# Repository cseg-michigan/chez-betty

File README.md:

Chez Betty
==========

Chez Betty is a mini, cooperative food store where users can deposit money to their account
and use it to purchase food and other items. The system is linked
to the UMich ldap server so users can swipe their M-Card to login.

UMich version is an homage to UCSD's [Chez Bob](http://chezbob.ucsd.edu/).
Chez Betty runs [here](http://chezbetty.store).

Chez Betty is written as a Python web app designed to run on a server with
a browser based user interface. It supports cash and credit card deposits. The
user interface expects a card swiper and barcode scanner to be attached to
the machine. See the list at the end of this README for products we use.
To test / demo the system without hardware, turn on "Demo mode" in the admin
interface.

Installation
------------

The Chez Betty application is developed using Python Pyramid. To get a
development environment set up, do the following:

1. Clone this repository

        git clone https://github.com/um-cseg/chez-betty.git

2. Install system dependencies:

        # Ubuntu 15.10
        sudo apt-get install postgresql postgresql-server-dev-9.4 libjpeg-dev
        # Ubuntu 16.10
        sudo apt-get install postgresql postgresql-server-dev-9.5 libjpeg-dev

1. Setup virtualenv with Python3:

        cd chez-betty

        # Python cannot decide on how it wants to do this. So
        # we have multiple iterations that we have tried.
        ## Way back:
        # virtualenv .
        ## Python3.3:
        # python3 -m venv .
        # ^ *not* pyvenv ., that installed python2 in my venv for w/e reason
        ## Newest (only do this with Python 3.4+):
        # pyvenv-3.5 venv
        ## Python 3.6 changes it again!
        #python3.6 -m venv
        ## And for 3.7
        python3.7 -m venv venv

        source venv/bin/activate

2. Install the dependencies:

        # Note, this step *must* be run before setup.py. The latter will use
        # easy_install to install requirements instead of pip, which will
        # break some packages (e.g. stripe). The argument should be the root
        # directory of the project.
        pip install -e .

2. Setup the development environment

        python setup.py develop

3. Update `development.ini` to set config information and passwords.

        cp development.ini.example development.ini
        [edit development.ini]

    You will want to use a postgres database. Likely, your development.ini file
    will need to be updated to have this for the database:

        sqlalchemy.url = postgresql://bradjc@localhost:5432/chezbetty

    To create that database, do something like:

        psql
        > create database chezbetty;

3. Setup the database:

        python chezbetty/initializedb.py development.ini

4. Install bower and bower-install

        # Note: Distro copies of node tend to fall behind really quickly.
        # You are better off using a copy of node/npm installed directly:
        # http://nodejs.org/
        # https://github.com/npm/npm
        sudo npm install bower bower-installer -g

5. Get all css/js dependencies

        bower-installer

4. Run the webserver:

        pserve development.ini
        # n.b. pserve will be in your path if your virtualenv is active

### LDAP

TODO: add information about how to setup LDAP connection.

### Bitcoin

TODO: add info about how to setup bitcoin/coinbase.

Usage
-----

View the client interface using

    http://127.0.0.1:6543

View the admin interface using

    http://127.0.0.1:6543/admin
    username: admin
    password: chezbettyadmin

Tools
-----

Chez Betty currently runs using:

- Intel Nuc with case - Running Ubuntu.
- [Magnetic Strip Reader](https://www.cdw.com/shop/products/MagTek-SureSwipe-Reader-USB-HID-Keyboard-Interface-magnetic-card-reader/1140626.aspx) - Acts as a keyboard input.
- [Barcode Scanner](https://www.cdw.com/shop/products/Motorola-LS2208-barcode-scanner-scanner-and-USB-cable-included/3021140.aspx) - Also keyboard input.
- [Touchscreen Monitor](http://www.amazon.com/ViewSonic-TD2220-22-Inch-LED-Lit-Display/dp/B009F1IKFC) - Acts as a mouse.

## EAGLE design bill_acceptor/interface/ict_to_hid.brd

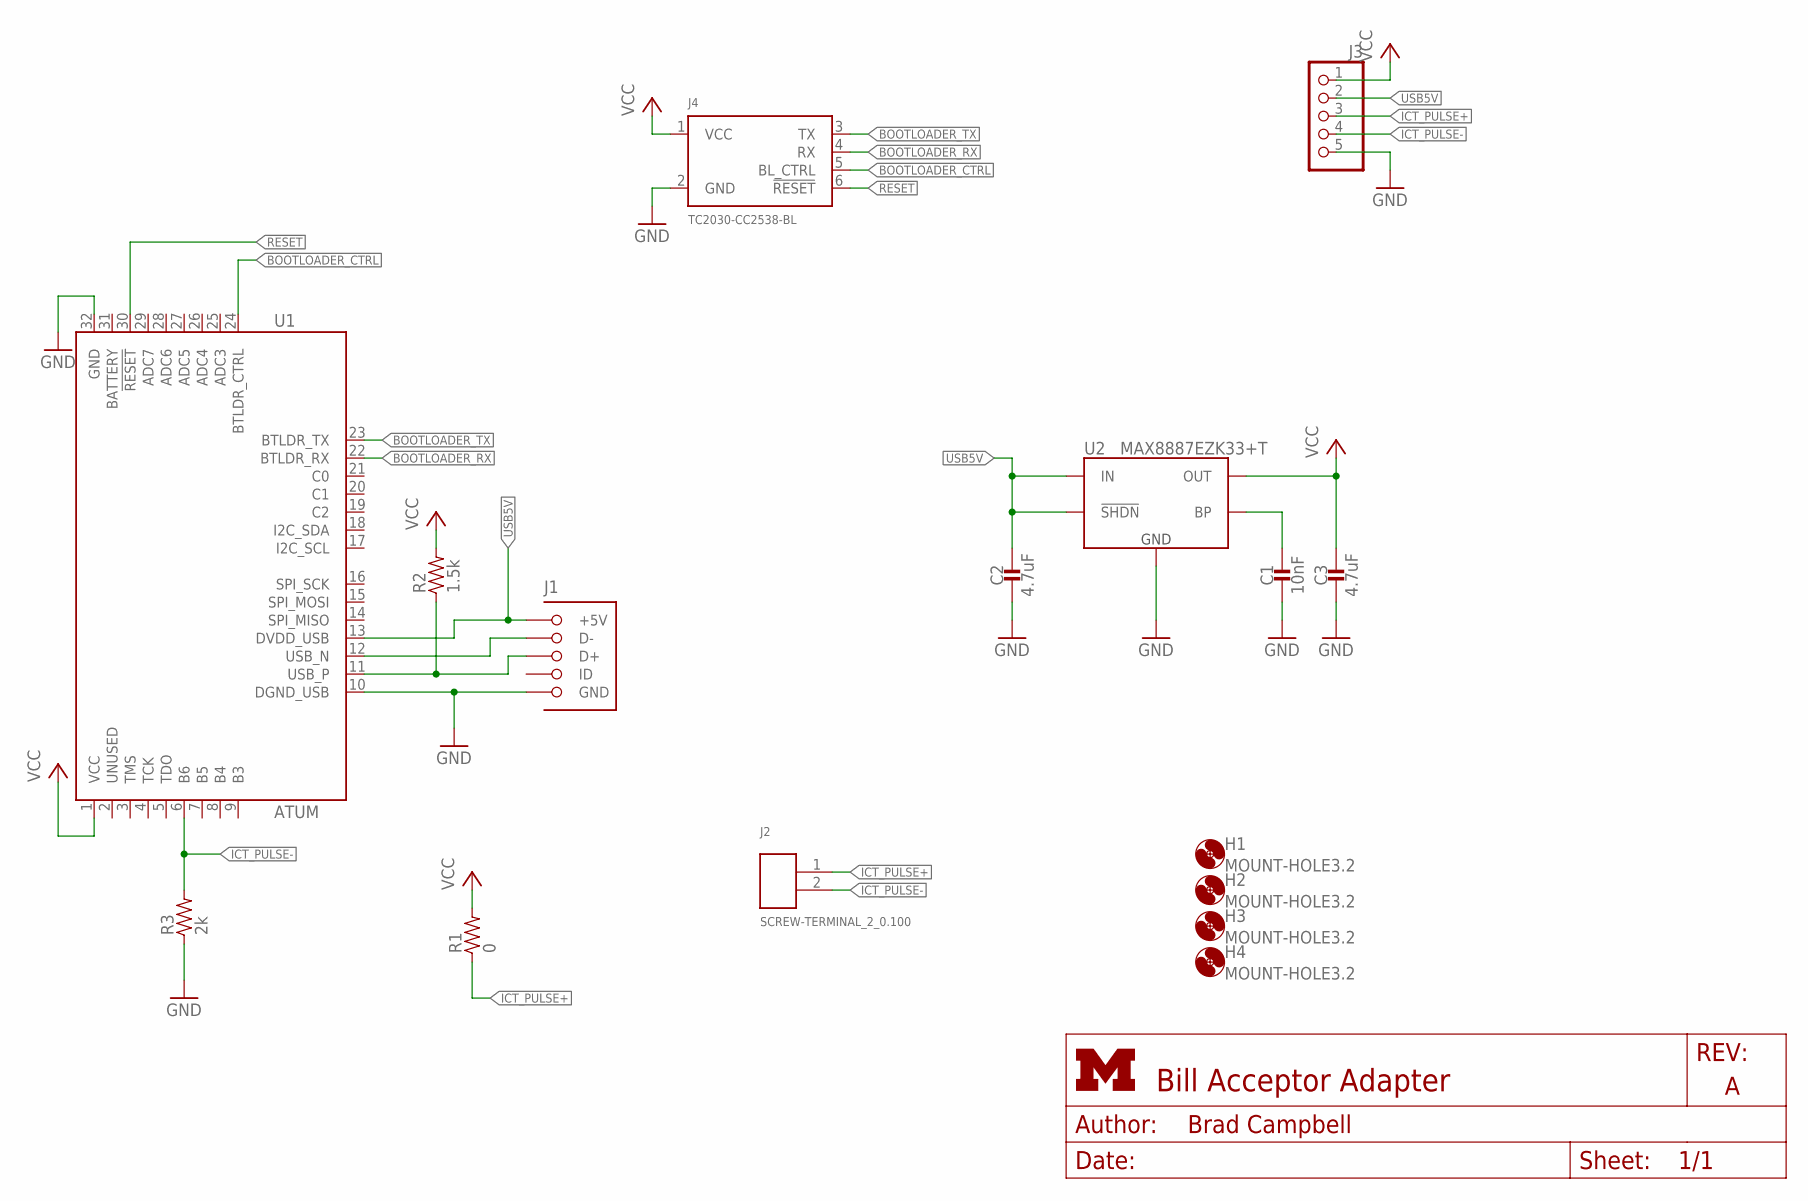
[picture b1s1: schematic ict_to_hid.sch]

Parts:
C1: 10nF; 0603_CAP
C2, C3: 4.7uF; 0603_CAP
H1, H2, H3, H4: MOUNT-HOLE3.2; 3,2
J1: MICRO_USB_B_HIROSE_ZX62R-B-5P; USB_MICRO_B-HIROSE-ZX62R-B-5P; MOUSER 798-ZX62R-B-5P
J2: SCREW-TERMINAL_2_0.100; CONN_BLOCK_2
J3: PINHD-1X5; 1X05
J4: TC2030-CC2538-BL; TC2030-IDC
R1: 0; 0603-RES
R2: 1.5k; 0603-RES
R3: 2k; 0603-RES
U1: ATUM
U2: MAX8887EZK33+T; SOT-23-5

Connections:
!RESET: J4.6 (!RESET), U1.30 (!RESET)
BOOTLOADER_CTRL: J4.5 (BL_CTRL), U1.24 (BTLDR_CTRL)
BOOTLOADER_RX: J4.4 (RX), U1.22 (BTLDR_RX)
BOOTLOADER_TX: J4.3 (TX), U1.23 (BTLDR_TX)
GND: C1.2, C2.2, C3.2, J1.5 (GND), J3.5, J4.2 (GND), R3.1, U1.10 (DGND_USB), U1.32 (GND), U2.2 (GND)
ICT_PULSE+: J2.1, J3.3, R1.1
ICT_PULSE-: J2.2, J3.4, R3.2, U1.6 (B6)
unnamed: C1.1, U2.4 (BP)
unnamed: J1.2 (D-), U1.12 (USB_N)
unnamed: J1.3 (D+), R2.1, U1.11 (USB_P)
USB5V: C2.1, J1.1 (+5V), J3.2, U1.13 (DVDD_USB), U2.1 (IN), U2.3 (!SHDN)
VCC: C3.1, J3.1, J4.1 (VCC), R1.2, R2.2, U1.1 (VCC), U2.5 (OUT)

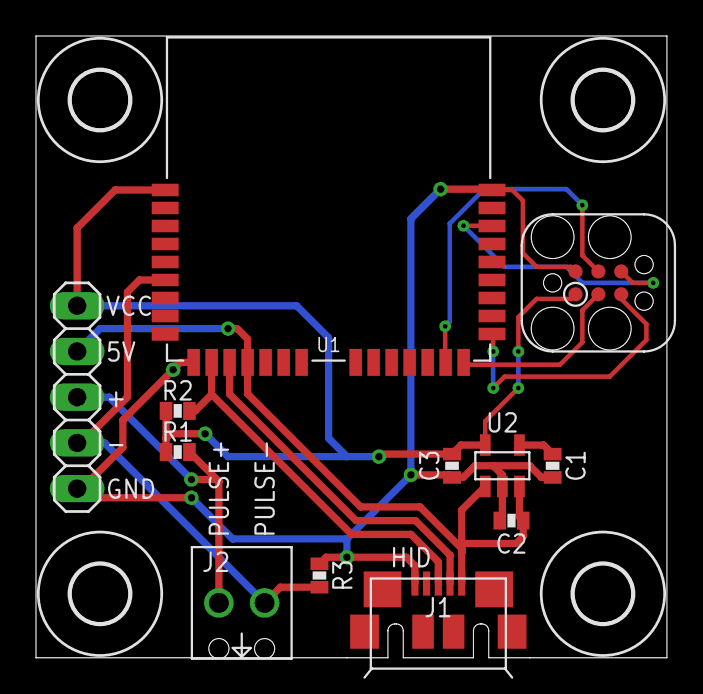
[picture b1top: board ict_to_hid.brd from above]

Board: 2 copper layers, 35.1 x 34.5 mm, 16 parts (0 on the bottom side), 12 nets.

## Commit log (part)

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2015-12-04 add support for adding purchases manually
2015-12-04 don't try to purchase items with 0 quantity
2015-12-05 Add top wall of shame to homepage
2015-12-05 Remove unused service account check
2015-12-05 if a user doesn't have any transactions, need to set count to 0 instead of None
2015-12-10 Send emails to new users when they join
    Closes #219
2015-12-10 new history notes
2015-12-11 Change over some of the trivial slow queries
2015-12-14 Add pop-up to homepage
2015-12-15 Add count to splash page
    Also up the font size because we can now
2015-12-17 add days since last purchase to users page
    hope its not too slow...
2015-12-18 fix for random 404 popup
    Tries to actually 404 on pages that don't exist, and redirects home on a
    page that might exist but doesn't. Should stop the random 404 flash
    errors from popping up as they won't be generated for missing .js.map
    files or favicon.ico.
2015-12-28 put javascript in a js file
    ...
2015-12-30 Add balance over time graph to user detail page
    Closes #229.
2016-01-06 Color user balances red when in debt
2016-01-24 add venv to gitignore
2016-01-25 clicked save too early
    also need libjpeg
2016-01-27 move item without barcode button
2016-01-27 better look, better balance total handling
2016-01-27 reorganize views
    make a public views section
2016-01-27 hide login form if already logged in
2016-01-27 redo terminal page
    - create only 1 page: purchase and deposit
    - make all actions ajax
    - get rid of the bajillion js files i made back in the day
    - clean things up a bit
2016-01-27 remove old javascript
2016-02-06 Had two div's with `id=alerts`, fix
2016-02-07 Remove unneeded text input filter
    Fixes #232.
2016-02-19 restore handler for new request
    oops. too much commented out in new UI change.
2016-02-22 display discounts/fees on admin index
2016-02-22 add account amounts to admin transactions page
2016-02-22 remove shopping list
    it was noise, didn't work
2016-02-22 remove weird click to clear alerts
2016-02-22 remove last traces of js date formatting
    closes #192
2016-02-22 show user fees and discount on user page
2016-02-22 fix floating point error in discount calc
    i learned something about how the decimal library works
2016-02-24 update splash text
2016-03-07 Sort descending in custom sort also
    Fixes #246.
2016-03-07 Filter deleted transactions in long-term balances
    I went through all the admin graphs and I think this was actually
    the only graph that was missing this [note that user detail views
    end up calling the same query]
    Closes #242.
2016-03-07 Add balance over time graph to user homepage
2016-03-07 Add FAQ entries for discout/tax
    Closes #241.
2016-03-08 Add [pshell] example to dev.ini
2016-03-12 fundraising 2
2016-03-15 Add terminal link to admin view
2016-03-15 Ignore MCard input while splash screen is live
2016-03-16 Add second click-through page
2016-03-18 Add e-mails for top 5 users to splash screen
2016-03-20 fix error handling in user details lookup
2016-03-20 add support for archiving users
2016-03-29 Make 'do you knows' mailto links
2016-03-30 Remove debt splash screen
2016-04-04 shorten name
2016-04-05 add safe contents to estimated net
2016-04-08 add yesterday box
2016-04-17 fix bug with WoS fee
    ...ooops my bad
2016-04-28 fix issue with initial glitch causing a dollar
    to be recorded
2016-05-04 Add basic Travis-CI support
    Doesn't quite validate the empty database like #259 would like
    because our existing initializedb.py pre-populates with some users
    and items [though no transactions].
2016-05-14 updates to terminal js
2016-05-14 added merging deposits
2016-05-15 fix two bugs with failed coin deposits
2016-05-15 separate disabled items on restock
    fixes #257
2016-05-15 show what is resocked when 1 item matched
    fixes #234
2016-05-15 add histograms
    fixes #161
2016-05-22 nice view for seeing deposits since last empty
    helps with making sure everything is working
2016-05-22 show deleted transactions in cashbox empty summary
2016-05-27 no more coins
    only removed button for now. the code is still there. if this change is
    permanent we should get rid of all of the code.
2016-06-01 Remove spurious prints, give debug a chance
2016-06-04 Add current items to user sidebar
2016-06-24 Don't show `other` tag if it's empty
    Closes #271.
2016-06-24 Add 'recently purchased items' to terminal
2016-06-26 add barcode and tag number to items page
2016-06-26 Use non-breaking hyphen for negatives
    Fixes #258.
2016-08-08 Add email to about page
2016-09-04 default to deposit all money to bank
    fixes #272
2016-09-04 added ability to select reimbursee for restocks
2016-09-04 update text on withdrawal page
2016-09-04 add ability to filter on reimbursements
2016-09-04 fix bug with undo restock
2016-09-05 add days since restock to items page
2016-09-05 remove old commented out deposit delete code
    can't delete a deposit anymore
2016-09-06 count only the archived balance when user archived
    fixes issue where admin panel displayed wrong amount for total archived
    balances
2016-09-08 fix bug with not being able to do inventory
2016-10-09 add year based history
2016-10-26 Update index queries to use kwargs
2016-11-04 Added Romanian language support.
    Created a new locale file with translated strings, and added a link
    to the home page for the new language support.
    Translations are not 100% perfect. They are completely
    understandable, but some messages have lost their spunk or have had
    their wording slightly changed. Some of the Romanian strings may
    be missing accents, or may be inconsistent with formal/informal
2016-11-15 plus de traductions
2016-11-25 who even likes positional arguments anyway?
    fixes #4aaa243dbdb7d7e213ea1e3d3f50d68ae63fa974
2016-12-11 more compact WoS box on front page
2016-12-12 Add notes field for reimbursements
2016-12-19 Revert "Use non-breaking hyphen for negatives"
    This reverts commit 072bc2b1c5227c1b51c3b65af9bcb5fa854f4b76.
    @ppannuto seems unwilling or unable to fix this. Wrapping doesn't seem
    like a worse problem then a bunch of giberish.
    Fixes #273
2017-01-16 Disabled debt splash
    It's been up for too long, I suspect people are just ignoring it now
2017-01-18 Mark variables modified in interrupt handlers as volatile
    Assembly's a pain to read, but once I found one (benign) example of things
    getting reordered, it felt worth it to mark these conservatively
    (on my machine, the assembly changed
    if (send == 1) {
    send = 0
    uint8_t local_count = count;
2017-02-18 Split up items list by availability
2017-03-09 add monthly detailed breakdowns
2017-03-31 quick fix for too long bad scans
2017-04-19 don't email arhived users when emailing all
2017-04-19 Added translations for German internationalization
2017-04-21 take down debt splash
2017-04-23 shipped bill acceptor board
2018-02-19 Arabic support (#315)
    * Added Basic files for Arabic Translation. Need to actually translate
    * Finished and checked translations up to item request
    * Finished and checked translations up to deposit
    * Finished translating up to purchase
    * Finished and checked up to base
    * Finished and checked translation for index
2018-05-16 This will never cease to astound me
    ```
    $ pyvenv-3.6 venv
    WARNING: the pyenv script is deprecated in favour of `python3.6 -m venv`
    ```
2018-05-19 need to list wheel explicitly now?
    made betty server happy
2019-04-08 handle booleans in item_edit_submit
    sales tax, bottle deposit, and sticky price are boolean fields that
    need to be converted from strings "on" and "off" to bools before
    updating the database.
2019-04-08 welcome back message
2019-04-11 add more items to the betty lore
2019-04-11 no need to show bitcoin amount anymore
2019-04-12 Betty is back!
2019-04-20 admin index: update summary details
2019-04-21 make cash withdrawal pretty
2019-04-21 clean up cashbox and safe page
2019-04-21 fix badscans table
2019-04-21 update edit user balance
2019-04-21 individual pool
2019-04-21 restock refresh
2019-04-24 Update views_admin.py
    Moved the global cost addition from wholesale price to sale price; this prevents global cost from messing up the max(old, new) wholesale price.
2019-04-25 Admins and Managers in good standing now get wholesale prices.
2019-04-29 Rename migration_1.22.0-1.23.0.sql to migration_1.23.2-1.24.0.sql
2019-04-29 remove a ton of old deposit code
    just no longer needed after the change the bill acceptor
2019-04-29 remove old debtors code
    from terminal index
2019-04-29 consolidate user role string code
    no need for it to be in views_admin and copied twice
2019-04-30 remove other uses of `roles`
2019-05-02 sort tags, only show enabled items
2019-05-02 Fixed corner case where cash box full email wouldn't send if new balance was exactly THRESHOLD + REPEAT_THRESHOLD
2019-05-03 boxes: show number of unique items in box
2019-05-04 Added barcode to the List Boxes barcode
2019-05-06 Added number of subitems and active subitems to list boxes view to fix overwritten changes
2019-05-08 show number of items per tag
2019-05-09 add more details to history
    show year-over-year and semester views
2019-05-21 add better error message to reset password
    You have to login at the terminal before creating a web account.
    Fixes #320
2019-05-22 show item barcode in creating boxes
    Fixes #284
2019-05-22 update text on login page
    Fixes #327
2019-05-22 show last time emails were sent
2019-05-23 include pools in estimated net calculation
2019-05-24 Updated the box and item edit form fields to not allow non-numeric characters for prices and vendor numbers; also limited the max number of decimal places for prices
2019-07-03 Changed add user purchase deposit to remove non-numeric characters from user-search-choice string (string had in front of the numeric value)
2019-07-09 auto-purchase items in cart if user times out
    This should handle cases where people scan items, walk away, but forget to hit
    the purchase button.
2019-07-09 Auto-build translations on deploy
    Fixes #318.
2019-07-10 point local DB update script to new url
2019-07-17 add timefilter helper for queries
2019-07-24 Changed terminal timeout to a dynamic 2min timer (reset every time an item is scanned or the user interacts with the interface); also updated capitalization in some tooltips on index page
2019-07-26 [CSS] Move image auto-scale code to common file
2019-08-13 Added OR condition for when bill acceptor doesn't send first character (temp fix)
2019-09-06 Fixed issue where terminal wouldn't show correct discount based on user group; fixed calculation mismatch for discounts (price shown on terminal for all discounts didn't match price charged); updated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
2019-09-07 Fixed views where debtor fee showed differently during purchase vs post-purchase vs in event page due to rounding (one decimal place is used in calculation, so should show everywhere)
2019-10-18 Implemented a less hacky bugfix for Issue #343 (non-empty debtor cart after clicking Purchase)
2019-11-21 Added debt reminder popup on debtor login
2019-11-21 Updated wrong line..
2019-12-28 Change debtor email threshold to less than -
2020-01-28 Added support for emailing debtors with a configurable threshold
2020-02-14 Somehow no changes were pushed in c87a75a98047e8fa32ca5580d19e3ed2f59ebb27...this is the change
2020-02-16 Added instruction prompt for users with <= 3 purchases and 0 all-time deposits
